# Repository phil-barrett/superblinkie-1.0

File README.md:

# superblinkie
Addressable LED arrays

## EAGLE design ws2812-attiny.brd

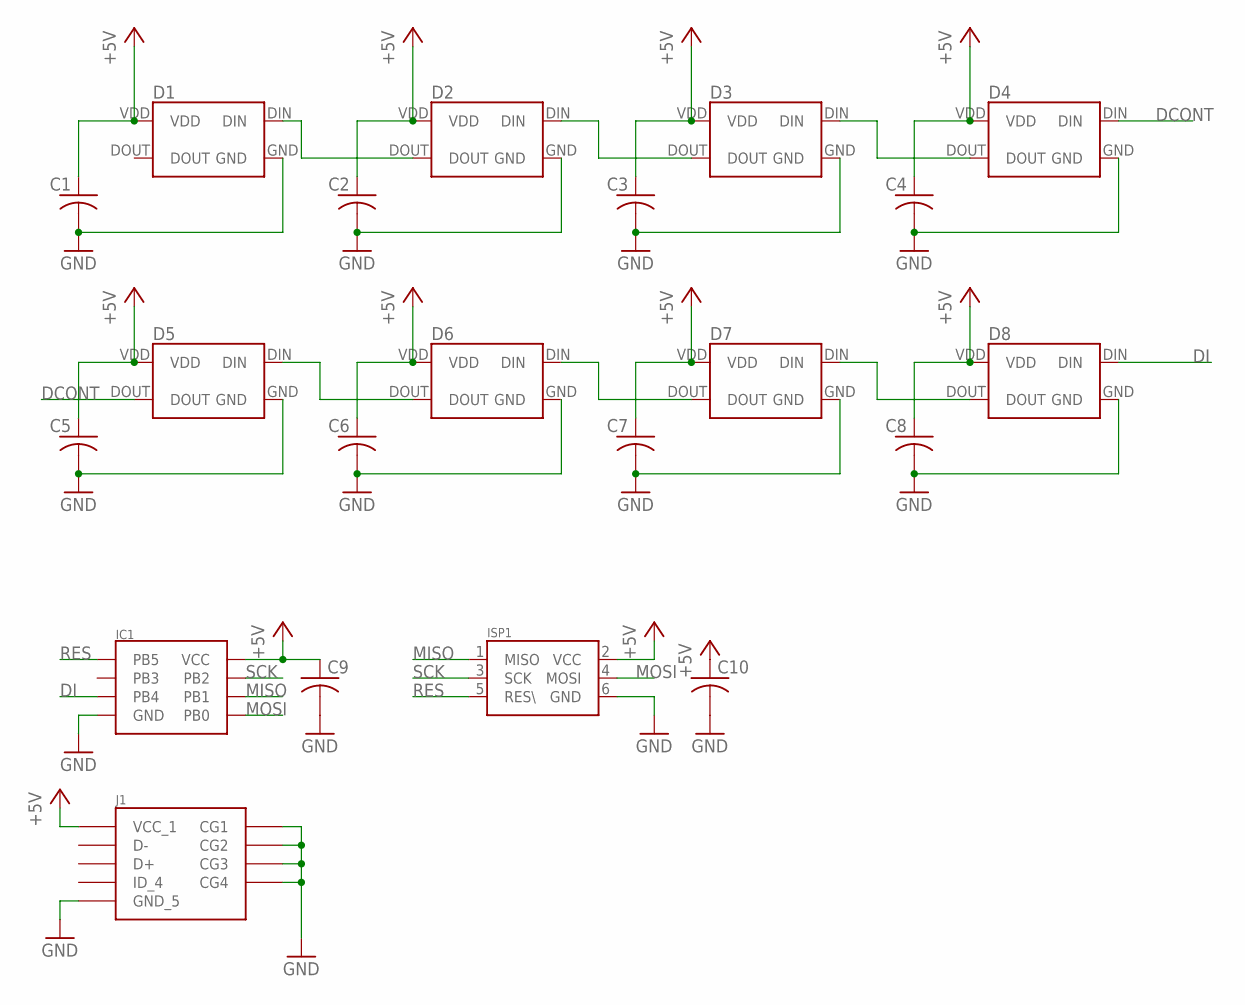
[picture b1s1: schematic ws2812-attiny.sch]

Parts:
C1, C2, C3, C4, C5, C6, C7, C8, C9, C10: C-USC1206; C1206
D1, D2, D3, D4, D5, D6, D7, D8: WS2812B
IC1: ATTINY85; ATTINY-8S2
ISP1: ISP-HEADER; 2X03
J1: USB_JAE_DX4R005HJ5R2000

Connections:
+5V: C1.1, C2.1, C3.1, C4.1, C5.1, C6.1, C7.1, C8.1, C9.1, C10.1, D1.VDD, D2.VDD, D3.VDD, D4.VDD, D5.VDD, D6.VDD, D7.VDD, D8.VDD, IC1.8 (VCC), ISP1.2 (VCC), J1.P$1 (VCC_1)
DCONT: D4.DIN, D5.DOUT
DI: D8.DIN, IC1.3 (PB4)
GND: C1.2, C2.2, C3.2, C4.2, C5.2, C6.2, C7.2, C8.2, C9.2, C10.2, D1.GND, D2.GND, D3.GND, D4.GND, D5.GND, D6.GND, D7.GND, D8.GND, IC1.4 (GND), ISP1.6 (GND), J1.P$5 (GND_5), J1.P$6 (CG4), J1.P$7 (CG3), J1.P$8 (CG2), J1.P$9 (CG1)
MISO: IC1.6 (PB1), ISP1.1 (MISO)
MOSI: IC1.5 (PB0), ISP1.4 (MOSI)
unnamed: D7.DIN, D8.DOUT
unnamed: D1.DIN, D2.DOUT
unnamed: D2.DIN, D3.DOUT
unnamed: D3.DIN, D4.DOUT
unnamed: D5.DIN, D6.DOUT
unnamed: D6.DIN, D7.DOUT
RES: IC1.1 (PB5), ISP1.5 (RES\)
SCK: IC1.7 (PB2), ISP1.3 (SCK)

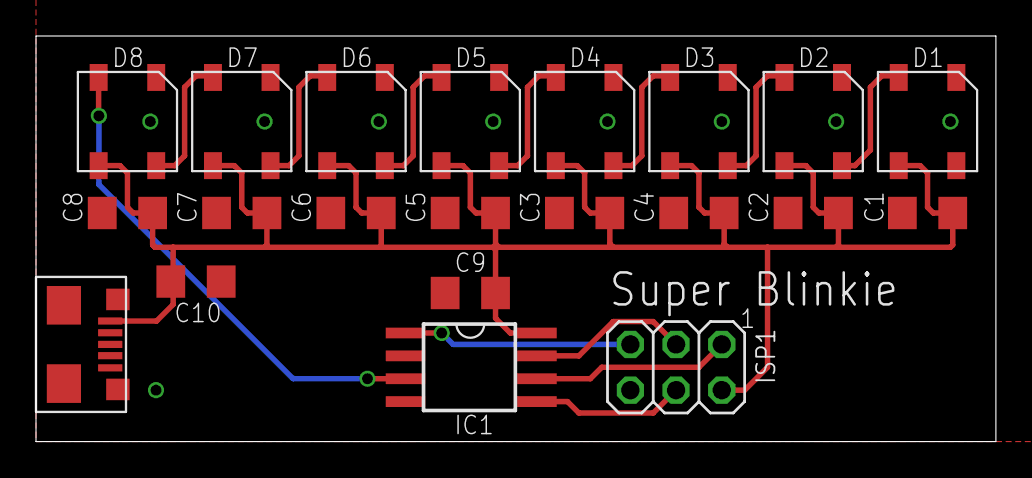
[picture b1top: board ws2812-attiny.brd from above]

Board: 2 copper layers, 53.3 x 22.5 mm, 21 parts (0 on the bottom side), 14 nets.
